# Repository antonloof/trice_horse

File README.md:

# trice_horse
look at my horse, it is blinking, give it a lake

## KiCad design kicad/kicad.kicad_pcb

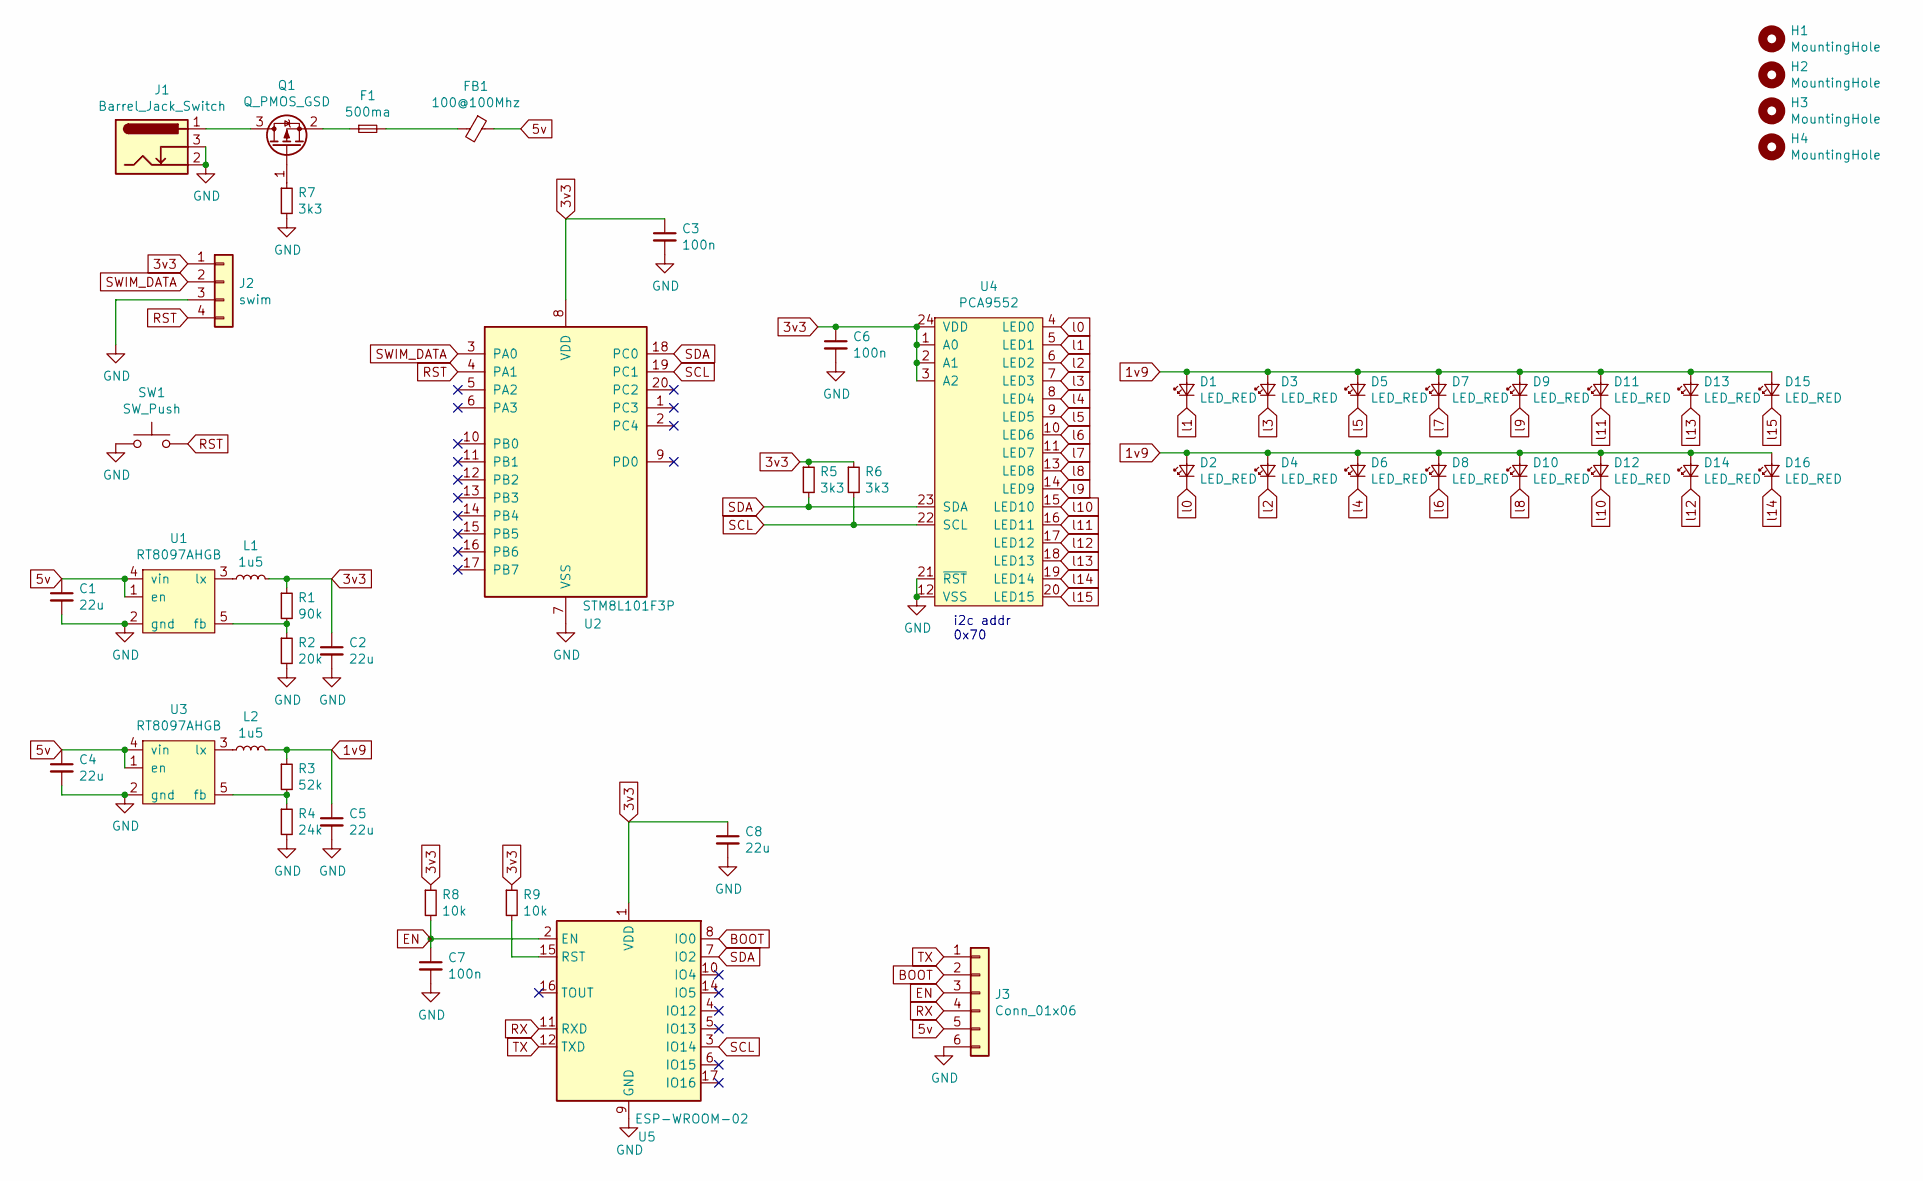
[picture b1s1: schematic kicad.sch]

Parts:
C1, C2, C4, C5, C8: 22u; C_0603_1608Metric_Pad1.05x0.95mm_HandSolder
C3, C6, C7: 100n; C_0603_1608Metric_Pad1.05x0.95mm_HandSolder
D1, D2, D3, D4, D5, D6, D7, D8, D9, D10, D11, D12, D13, D14, D15, D16: LED_RED; LED_D5.0mm
F1: 500ma; Fuse_1206_3216Metric_Pad1.42x1.75mm_HandSolder
FB1: 100@100Mhz; L_0805_2012Metric_Pad1.15x1.40mm_HandSolder
H1, H2, H3, H4: MountingHole; MountingHole_3.2mm_M3
J1: Barrel_Jack_Switch; BarrelJack_Horizontal
J2: swim; TSM-104-01-L-SH
J3: Conn_01x06; TSM-106-01-L-SH
L1, L2: 1u5; L_Wuerth_WE-PD-Typ-7345
Q1: Q_PMOS_GSD; SOT-23_Handsoldering
R1: 90k; R_0603_1608Metric_Pad1.05x0.95mm_HandSolder
R2: 20k; R_0603_1608Metric_Pad1.05x0.95mm_HandSolder
R3: 52k; R_0603_1608Metric_Pad1.05x0.95mm_HandSolder
R4: 24k; R_0603_1608Metric_Pad1.05x0.95mm_HandSolder
R5, R6, R7: 3k3; R_0603_1608Metric_Pad1.05x0.95mm_HandSolder
R8, R9: 10k; R_0603_1608Metric_Pad1.05x0.95mm_HandSolder
SW1: SW_Push; push_sw_purple
U1, U3: RT8097AHGB; SOT-23-5_HandSoldering
U2: STM8L101F3P; TSSOP-20_4.4x6.5mm_P0.65mm
U4: PCA9552; TSSOP-24_4.4x7.8mm_P0.65mm
U5: ESP-WROOM-02

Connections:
1v9: C5.1, D1.2 (A), D2.2 (A), D3.2 (A), D4.2 (A), D5.2 (A), D6.2 (A), D7.2 (A), D8.2 (A), D9.2 (A), D10.2 (A), D11.2 (A), D12.2 (A), D13.2 (A), D14.2 (A), D15.2 (A), D16.2 (A), L2.2, R3.1
3v3: C2.1, C3.1, C6.1, C8.1, J2.1, L1.2, R1.1, R5.1, R6.1, R8.1, R9.1, U2.8 (VDD), U4.1 (A0), U4.2 (A1), U4.3 (A2), U4.24 (VDD), U5.1 (VDD)
5v: C1.1, C4.1, FB1.1, J3.5, U1.1 (en), U1.4 (vin), U3.1 (en), U3.4 (vin)
BOOT: J3.2, U5.8 (IO0)
EN: C7.1, J3.3, R8.2, U5.2 (EN)
GND: C1.2, C2.2, C3.2, C4.2, C5.2, C6.2, C7.2, C8.2, J1.2, J1.3, J2.3, J3.6, R2.2, R4.2, R7.2, SW1.1, U1.2 (gnd), U2.7 (VSS), U3.2 (gnd), U4.12 (VSS), U4.21 (~RST), U5.9 (GND), U5.13 (GND), U5.18 (GND), U5.19 (GND)
unnamed: F1.1, Q1.2 (S)
unnamed: F1.2, FB1.2
unnamed: J1.1, Q1.3 (D)
unnamed: L1.1, U1.3 (lx)
unnamed: L2.1, U3.3 (lx)
unnamed: Q1.1 (G), R7.1
unnamed: R1.2, R2.1, U1.5 (fb)
unnamed: R3.2, R4.1, U3.5 (fb)
unnamed: R9.2, U5.15 (RST)
RST: J2.4, SW1.2, U2.4 (PA1)
RX: J3.4, U5.11 (RXD)
SCL: R6.2, U2.19 (PC1), U4.22 (SCL), U5.3 (IO14)
SDA: R5.2, U2.18 (PC0), U4.23 (SDA), U5.7 (IO2)
SWIM_DATA: J2.2, U2.3 (PA0)
TX: J3.1, U5.12 (TXD)
l0: D2.1 (K), U4.4 (LED0)
l1: D1.1 (K), U4.5 (LED1)
l2: D4.1 (K), U4.6 (LED2)
l3: D3.1 (K), U4.7 (LED3)
l4: D6.1 (K), U4.8 (LED4)
l5: D5.1 (K), U4.9 (LED5)
l6: D8.1 (K), U4.10 (LED6)
l7: D7.1 (K), U4.11 (LED7)
l8: D10.1 (K), U4.13 (LED8)
l9: D9.1 (K), U4.14 (LED9)
l10: D12.1 (K), U4.15 (LED10)
l11: D11.1 (K), U4.16 (LED11)
l12: D14.1 (K), U4.17 (LED12)
l13: D13.1 (K), U4.18 (LED13)
l14: D16.1 (K), U4.19 (LED14)
l15: D15.1 (K), U4.20 (LED15)

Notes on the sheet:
i2c addr 0x70

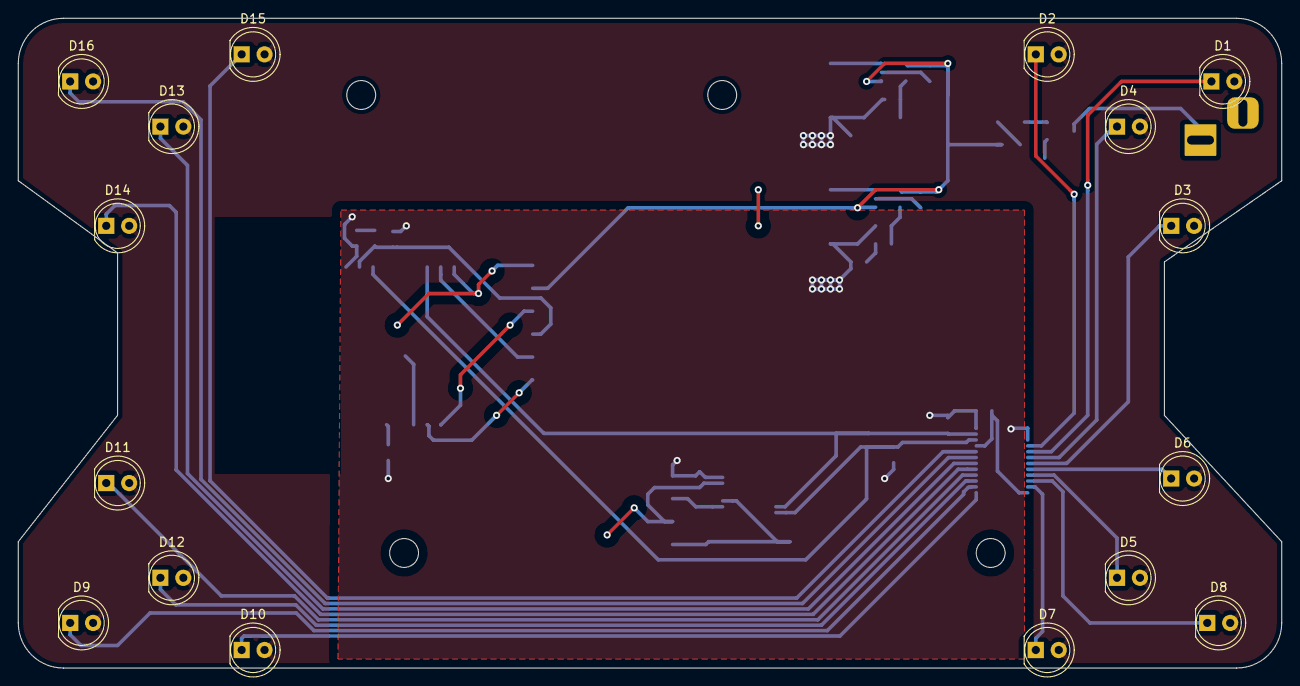
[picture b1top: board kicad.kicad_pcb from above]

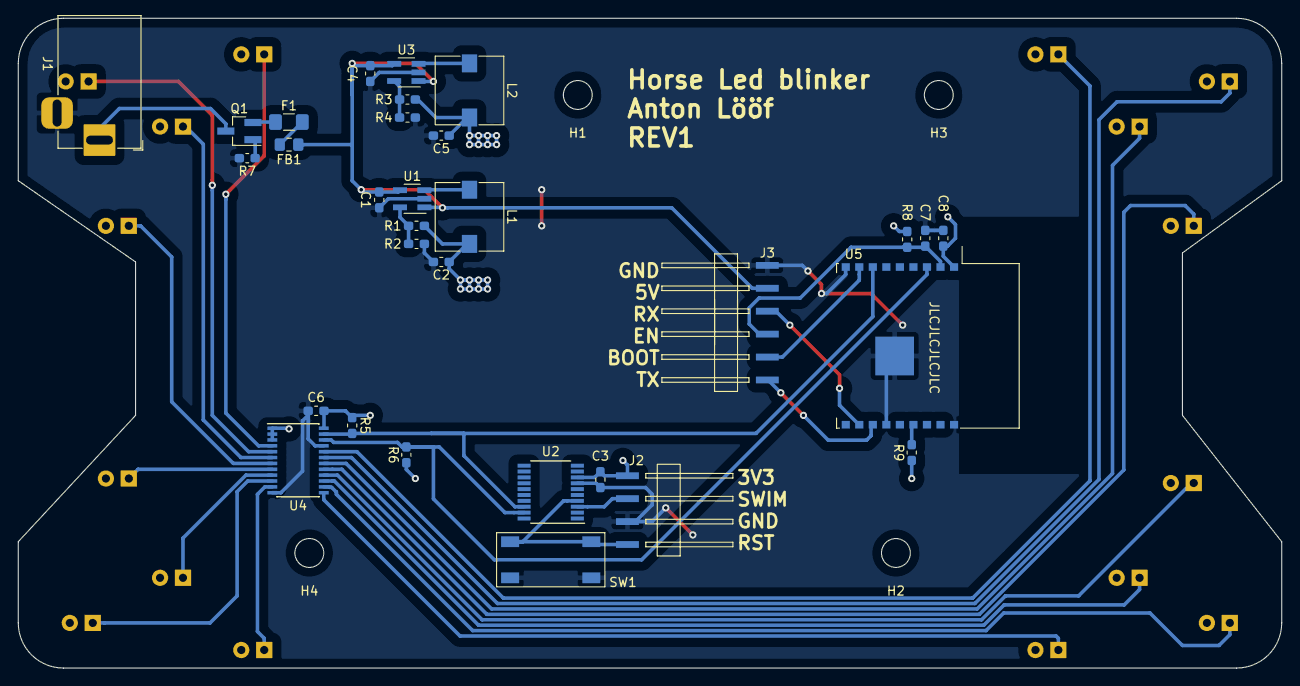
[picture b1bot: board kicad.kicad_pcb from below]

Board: 2 copper layers, 140.0 x 72.0 mm, 51 parts (35 on the bottom side), 37 nets.

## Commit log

2021-06-04 Add kicad
2021-06-04 Rm shit files
2021-06-27 Add SW. Update schema with bodge
    IT NOW WORKS
